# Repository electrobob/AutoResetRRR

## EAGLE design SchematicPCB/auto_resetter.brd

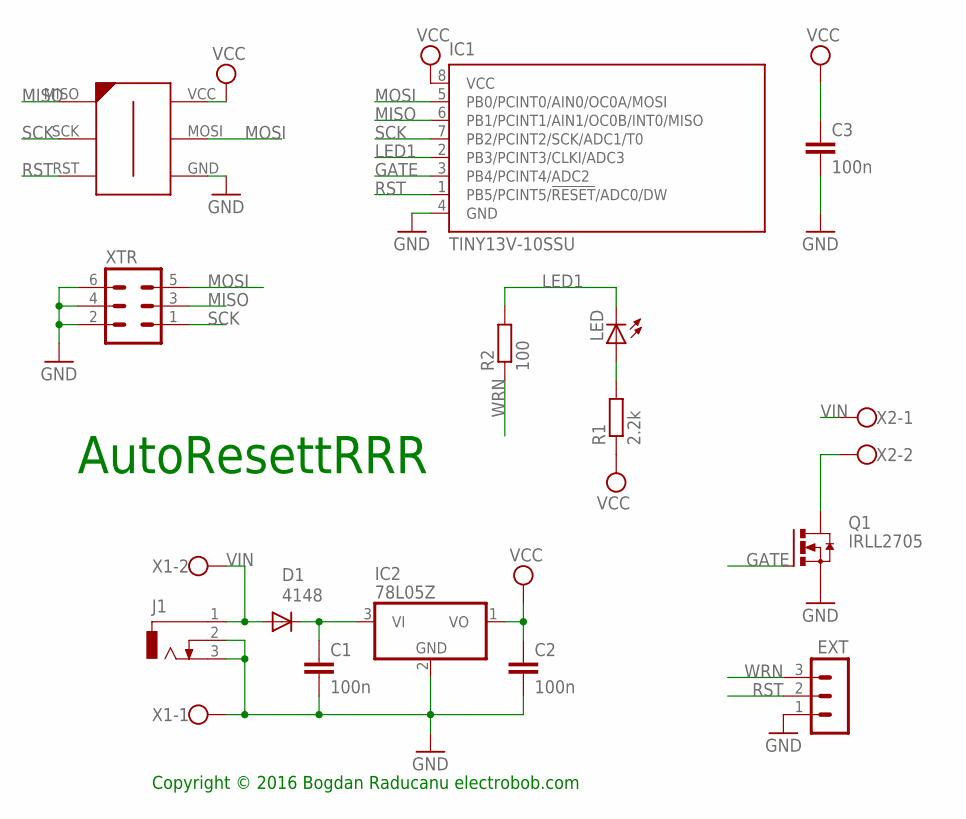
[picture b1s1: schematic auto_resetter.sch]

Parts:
C1, C2, C3: 100n; C0805
D1: 4148; MINIMELF
EXT: MA03-1
IC1: TINY13V-10SSU; 8S1
IC2: 78L05Z; TO92
J1: DCJ0303
LED: LED3MM
Q1: IRLL2705; SOT223
R1: 2.2k; M0805
R2: 100; M0805
U$1: AVR-ISP-6-EDGE; 6PAD_ISP
X1, X2: W237-102
XTR: MA03-2

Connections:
GATE: IC1.3 (PB4/PCINT4/ADC2), Q1.1 (G)
GND: C1.2, C2.2, C3.2, EXT.1, IC1.4 (GND), IC2.2 (GND), J1.2, J1.3, Q1.3 (S), U$1.GND, X1.1, XTR.2, XTR.4, XTR.6
LED1: IC1.2 (PB3/PCINT3/CLKI/ADC3), LED.K (C), R2.2
MISO: IC1.6 (PB1/PCINT1/AIN1/OC0B/INT0/MISO), U$1.MISO, XTR.3
MOSI: IC1.5 (PB0/PCINT0/AIN0/OC0A/MOSI), U$1.MOSI, XTR.5
unnamed: C1.1, D1.C, IC2.3 (VI)
unnamed: LED.A, R1.2
unnamed: Q1.2 (D), Q1.4 (D), X2.2
RST: EXT.2, IC1.1 (PB5/PCINT5/!RESET!/ADC0/DW), U$1.RST
SCK: IC1.7 (PB2/PCINT2/SCK/ADC1/T0), U$1.SCK, XTR.1
VCC: C2.1, C3.1, IC1.8 (VCC), IC2.1 (VO), R1.1, U$1.VCC
VIN: D1.A, J1.1, X1.2, X2.1
WRN: EXT.3, R2.1

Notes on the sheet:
Copyright © 2016 Bogdan Raducanu electrobob.com
AutoResettRRR

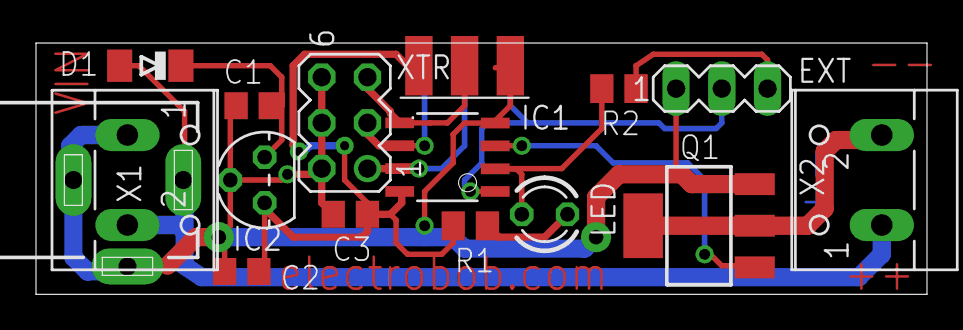
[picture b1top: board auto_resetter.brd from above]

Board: 2 copper layers, 49.5 x 14.0 mm, 16 parts (1 on the bottom side), 13 nets.

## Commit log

2016-05-05 :lollipop: Added .gitattributes & .gitignore files
2016-05-05 Auto Reset your misbehaving devices
2016-05-28 Updated SF and FW
